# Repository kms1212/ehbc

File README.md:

# !IMPORTANT: This project is migrated to Organization [ExtensibleHomeBrewComputer](https://github.com/ExtensibleHomeBrewComputer).

**ARCHIVED**

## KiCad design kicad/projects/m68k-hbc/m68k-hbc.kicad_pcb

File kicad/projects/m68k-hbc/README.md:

# EHBC Motherboard

## Main Goals
- A rich-function homebrew computer with completely extensible specification
- ATX-dimension compatible motherboard
- Configurable firmware
- Dual-boot function with Linux and custom multitasking OS
- Four 72-pin SIMM DRAM slots
- Rich peripheral interconnection features
  - MMIO with custom address configuration
  - Custom PCI-like expansion port (PEP, Peripheral Expansion Port)
  - 16-bit ISA bus
  - 8/16-bit PP Bus for low-speed peripherals
  - Floppy, IDE, RS232, UART, USB, Ethernet, Audio, etc.
- Advanced Memory Features
  - DRAM Controller with FPM and Read-Modify-Write support
  - 8-channel DMA support
- TBD

## Major ICs
- Main CPU MC68030 (@ 25, 33, 50MHz)
- Floating-point coprocessor MC68882 (@ 25, 33, 50MHz)
- Two EPF6016QC240 implementing some important features, as follows:
  - DRAM & 8-Channel DMA Controller with Cache
  - System Bus Controller (Processor Local Bus, PEP, ISA, OPB, ATA)
- ATMega32-16P working as a System Master Controller
- RTL8019AS ethernet controller
- CS4231A audio codec
- SL811HS USB host controller
- MC68901 MFP (system timer, USART, and GPIO or interrupt)
- VT82C42 keyboard and mouse controller
- PC8477BV floppy disk controller
- DS1307 RTC
- 25LC256 EEPROM
- PAC1932 power monitor
- EMC1701 power monitor with temperature sensor
- ADP5050 programmable DC-DC buck converter
- MX8315 configurable clock generator
- Auxillary ICS551, 542, and 501s for clock generation
- TBD

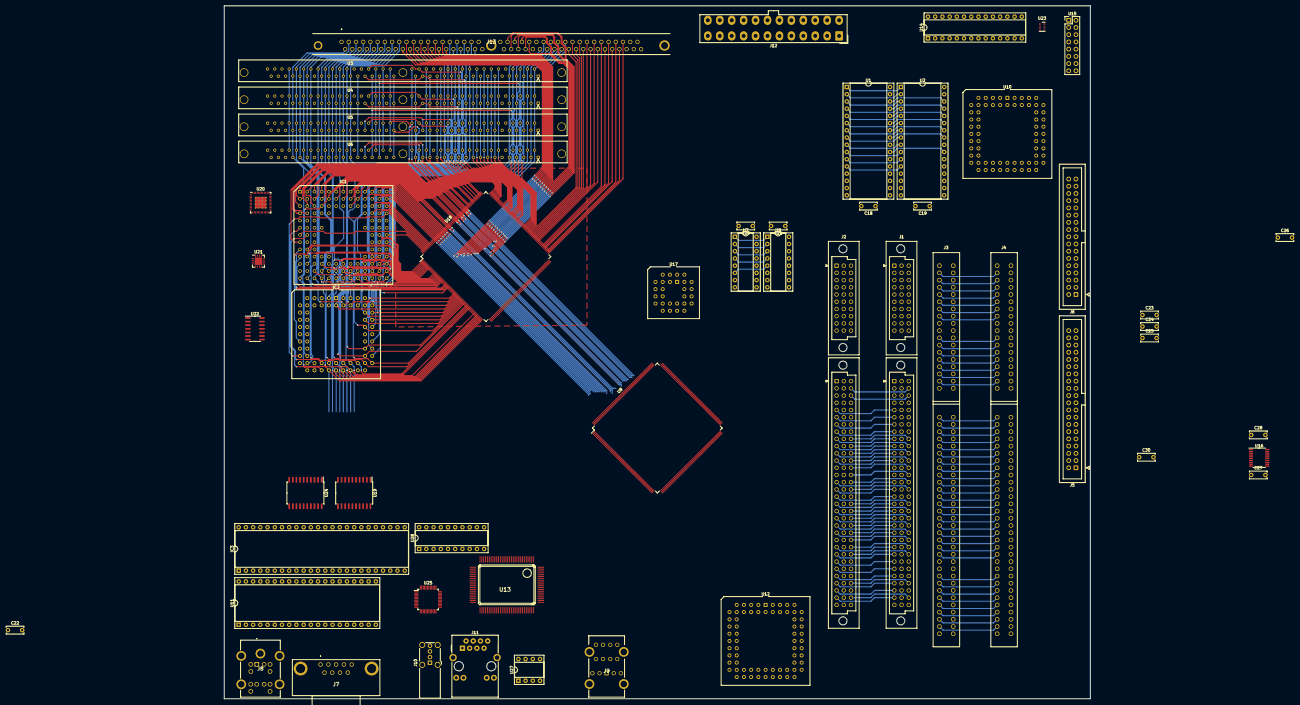
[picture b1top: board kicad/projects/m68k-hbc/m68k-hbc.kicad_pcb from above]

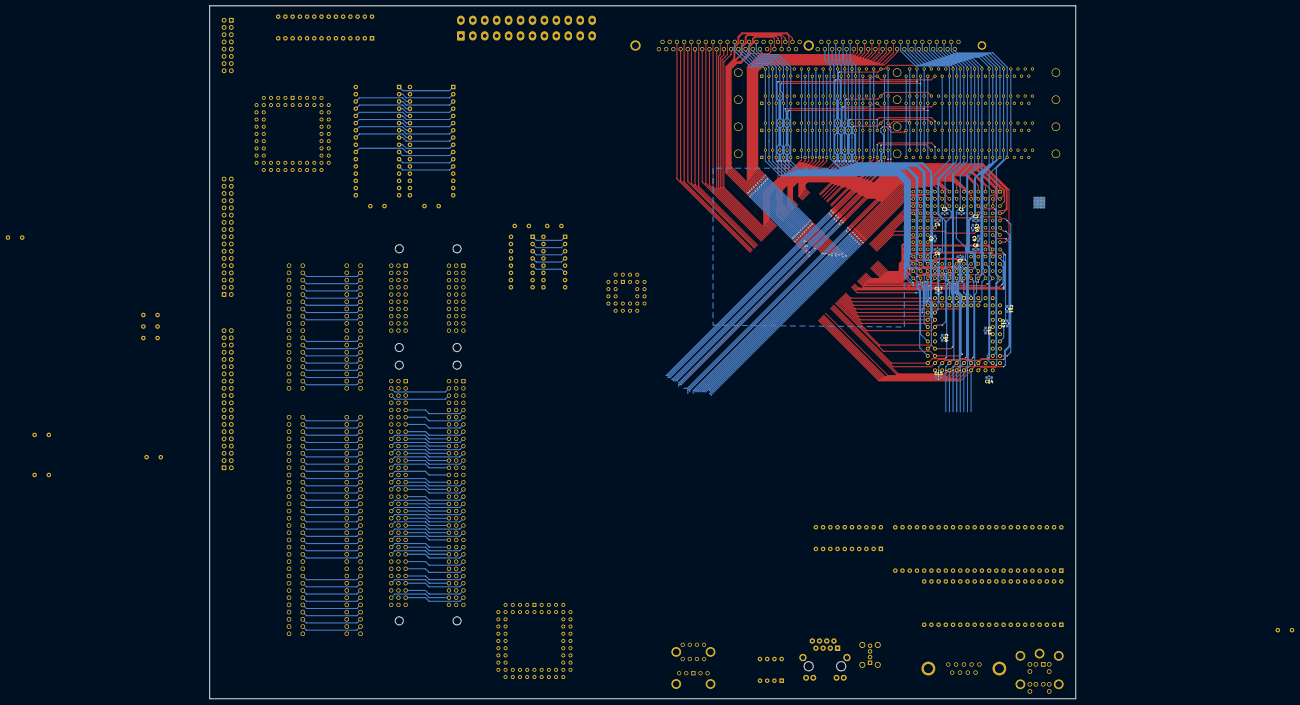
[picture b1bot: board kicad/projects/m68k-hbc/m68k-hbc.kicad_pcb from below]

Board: 6 copper layers, 304.8 x 243.8 mm, 72 parts (17 on the bottom side), 227 nets.

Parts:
C1, C2, C3, C4, C5, C6, C7, C8, C9, C10, C11, C12, C13, C14, C15, C16, C17: 100n; C_0603_1608Metric_Pad1.08x0.95mm_HandSolder
C18, C19, C20, C21, C22, C23, C24, C25, C26, C27, C28, C30: 100n; C_Disc_D6.0mm_W2.5mm_P5.00mm
IC1: MC68030RC; PGA128
IC2: MC68881FN; PLCC-68_THT-Socket
IC3: MC68901P; DIP-48_W15.24mm_Socket
J1, J2: PEP_Data_DIN41612_3x32; PEP_Board
J3, J4: Bus_ISA_16bit; ISA_16bit
J5: IDC_PATA; IDC-Header_2x20_P2.54mm_Vertical
J6: IDC_FDD; IDC-Header_2x17_P2.54mm_Vertical
J7: 5747840-4; 57478404
J8: KMDGX-6SG_P-S4N; KMDGX6SGPS4N
J9: STX-4335-5BGP-S1; STX43355BGPS1
J10: USB_A; USB_A_Wuerth_614004134726_Horizontal
J11: RJ45_Bel_SI-60062-F
J12: ATX-24; Molex_Mini-Fit_Jr_5566-24A_2x12_P4.20mm_Vertical
J13: SIMM80_Cache; 58220304
U1, U2: SST39SF040; DIP-32_W15.24mm_Socket
U3, U4, U5, U6: SIMM72
U7, U9: 74LS138; DIP-16_W7.62mm_Socket
U8, U18: EPF6016QC240; PQFP-240_32.1x32.1mm_P0.5mm
U10: PC8477BV; PLCC-68_THT-Socket
U11: VT82C42; DIP-40_W15.24mm_Socket
U12: CS4231A; PLCC-68_THT-Socket
U13: RTL8019AS
U14: ATmega328P-P; DIP-28_W7.62mm_Socket
U15: SYS_Header; PinHeader_2x08_P2.54mm_Vertical
U16: PCA9564; TSSOP-20_4.4x6.5mm_P0.65mm
U17: TP3465V; PLCC-28_THT-Socket
U19, U24: 74LS245; SOIC-20W_7.5x12.8mm_P1.27mm
U20: ADP5050ACPZ; LFCSP-48-1EP_7x7mm_P0.5mm_EP4.1x4.1mm_ThermalVias
U21: PAC1932x-xJQ; UQFN-16-1EP_4x4mm_P0.65mm_EP2.6x2.6mm
U22: MX8315MC; SOIC-14_3.9x8.7mm_P1.27mm
U23: STM6601; TDFN-12_2x3mm_P0.5mm
U25: SL811HST; TQFP-48_7x7mm_P0.5mm
U27: 93CxxC; DIP-8_W7.62mm_Socket
U28: PAL16L8; DIP-20_W7.62mm_Socket

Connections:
+3.3V: J1.Pa8 (+3.3V), J1.Pa9 (+3.3V), J1.Pb8 (+3.3V), J1.Pb9 (+3.3V), J1.Pc8 (+3.3V), J1.Pc9 (+3.3V), J2.Pa8 (+3.3V), J2.Pa9 (+3.3V), J2.Pb8 (+3.3V), J2.Pb9 (+3.3V), J2.Pc8 (+3.3V), J2.Pc9 (+3.3V), J12.1 (+3.3V), J12.2 (+3.3V), J12.12 (+3.3V), J12.13 (+3.3V)
+5V: IC2.18 (SIZE), IC2.26 (A0), J1.Pa5 (+5V), J1.Pa6 (+5V), J1.Pa7 (+5V), J1.Pb7 (+5V), J1.Pc5 (+5V), J1.Pc6 (+5V), J1.Pc7 (+5V), J2.Pa5 (+5V), J2.Pa6 (+5V), J2.Pa7 (+5V), J2.Pb7 (+5V), J2.Pc5 (+5V), J2.Pc6 (+5V), J2.Pc7 (+5V), J3.3 (+5V), J3.29 (VCC), J3.78 (+5V), J4.3 (+5V), J4.29 (VCC), J4.78 (+5V), J12.4 (+5V), J12.6 (+5V), J12.21 (+5V), J12.22 (+5V), J12.23 (+5V), U1.31 (PGM), U2.31 (PGM), U9.6 (E3), U13.13 (SA7), U13.15 (SA8), U13.65 (JP)
+5VCPU: C1.1, C2.1, C3.1, C4.1, C5.1, C6.1, C7.1, C8.1, C9.1, C10.1, C11.1, C12.1, C13.1, C14.1, C15.1, C16.1, C17.1, C18.1, C19.1, IC1.C06 (VCC@1), IC1.D04 (VCC@2), IC1.D10 (VCC@3), IC1.F02 (VCC@4), IC1.F11 (VCC@5), IC1.H03 (VCC@6), IC1.H11 (VCC@7), IC1.K04 (VCC@8), IC1.K10 (VCC@9), IC1.L06 (VCC@10), IC2.10 (VCC@1), IC2.16 (VCC@2), IC2.17 (VCC@3), IC2.27 (VCC@4), IC2.43 (VCC@5), IC2.52 (VCC@6), IC2.53 (VCC@7), IC2.61 (VCC@8)
+5VMEM: J13.39 (+5V), J13.40 (+5V), J13.41 (+5V), U1.32 (VCC), U2.32 (VCC), U3.10 (+3.3V/+5V), U3.30 (+3.3V/+5V), U3.59 (+3.3V/+5V), U4.10 (+3.3V/+5V), U4.30 (+3.3V/+5V), U4.59 (+3.3V/+5V), U5.10 (+3.3V/+5V), U5.30 (+3.3V/+5V), U5.59 (+3.3V/+5V), U6.10 (+3.3V/+5V), U6.30 (+3.3V/+5V), U6.59 (+3.3V/+5V)
+5VPER: C20.1, C21.1, C22.1, C23.1, C24.1, C25.1, C26.1, C27.1, C28.1, C30.1, IC3.11 (VCC), U7.16 (VCC), U9.16 (VCC), U10.18 (+5V), U10.60 (+5V), U10.68 (+5V), U11.40 (+5V), U13.6 (+5V), U13.17 (+5V), U13.47 (+5V), U13.57 (+5V), U13.70 (+5V), U13.89 (+5V), U14.7 (VCC), U16.20 (VCC), U17.28 (VCC), U19.20 (VCC), U22.9 (DVDD), U24.20 (VCC), U27.6 (ORG), U27.8 (VCC)
+5VSB: J1.Pa4 (+5VSB), J2.Pa4 (+5VSB), J12.9 (+5VSB), U23.1 (Vcc)
+12V: J1.Pa2 (+12V), J1.Pa3 (+12V), J1.Pb2 (+12V), J1.Pb3 (+12V), J1.Pc2 (+12V), J1.Pc3 (+12V), J2.Pa2 (+12V), J2.Pa3 (+12V), J2.Pb2 (+12V), J2.Pb3 (+12V), J2.Pc2 (+12V), J2.Pc3 (+12V), J3.9 (+12V), J4.9 (+12V), J12.10 (+12V), J12.11 (+12V)
-5V: J1.Pc4 (-5V), J2.Pc4 (-5V), J3.5 (-5V), J4.5 (-5V)
-12V: J1.Pb4 (-12V), J2.Pb4 (-12V), J3.7 (-12V), J4.7 (-12V), J12.14 (-12V)
/Bus/A0: IC1.A02 (A0), IC3.2 (RS1), U10.7 (A0), U11.9 (A0), U12.10 (A0), U16.14 (A0), U18.197 (IO), U25.42 (A0)
/Bus/A1: IC1.C04 (A1), IC2.25 (A1), IC3.3 (RS2), U1.12 (A0), U2.12 (A0), U10.8 (A1), U12.9 (A1), U16.15 (A1), U18.203 (IO)
/Bus/A2: IC1.D13 (A2), IC2.24 (A2), IC3.4 (RS3), U1.11 (A1), U2.11 (A1), U10.10 (A2), U18.237 (IO)
/Bus/A3: IC1.D12 (A3), IC2.23 (A3), IC3.5 (RS4), U1.10 (A2), U2.10 (A2), U18.236 (IO)
/Bus/A4: IC1.C13 (A4), IC2.22 (A4), IC3.6 (RS5), U1.9 (A3), U2.9 (A3), U18.234 (IO)
/Bus/A5: IC1.C12 (A5), U1.8 (A4), U2.8 (A4), U18.233 (IO)
/Bus/A6: IC1.D11 (A6), U1.7 (A5), U2.7 (A5), U18.235 (IO)
/Bus/A7: IC1.B13 (A7), U1.6 (A6), U2.6 (A6), U18.228 (IO)
/Bus/A8: IC1.B12 (A8), U1.5 (A7), U2.5 (A7), U7.1 (A0), U9.1 (A0), U18.227 (IO)
/Bus/A9: IC1.C11 (A9), U1.27 (A8), U2.27 (A8), U7.2 (A1), U9.2 (A1), U18.232 (IO)
/Bus/A10: IC1.A13 (A10), U1.26 (A9), U2.26 (A9), U7.3 (A2), U9.3 (A2), U18.224 (IO)
/Bus/A11: IC1.C10 (A11), U1.23 (A10), U2.23 (A10), U7.6 (E3), U9.5 (E2), U18.231 (IO)
/Bus/A12: IC1.B11 (A12), J13.18 (A0), U1.25 (A11), U2.25 (A11), U18.226 (IO)
/Bus/A13: IC1.A12 (A13), J13.19 (A1), U1.4 (A12), U2.4 (A12), U18.223 (IO)
/Bus/A14: IC1.B10 (A14), J13.20 (A2), U1.28 (A13), U2.28 (A13), U18.225 (IO)
/Bus/A15: IC1.A11 (A15), J13.21 (A3), U1.29 (A14), U2.29 (A14), U18.222 (IO)
/Bus/A16: IC1.B09 (A16), J13.22 (A4), U1.3 (A15), U2.3 (A15), U18.220 (IO)
/Bus/A17: IC1.A10 (A17), J13.23 (A5), U1.2 (A16), U2.2 (A16), U18.221 (IO)
/Bus/A18: IC1.C08 (A18), J13.24 (A6), U1.30 (A17), U2.30 (A17), U18.218 (IO)
/Bus/A19: IC1.A09 (A19), J13.25 (A7), U1.1 (A18), U2.1 (A18), U18.219 (IO)
/Bus/A20: IC1.B08 (A20), J13.26 (A8), U18.217 (IO)
/Bus/A21: IC1.A08 (A21), J13.27 (A9), U18.215 (IO)
/Bus/A22: IC1.B07 (A22), J13.28 (A10), U18.214 (IO)
/Bus/A23: IC1.A07 (A23), J13.29 (A11), U18.213 (IO)
/Bus/A24: IC1.A06 (A24), J13.30 (A12), U18.207 (IO)
/Bus/A25: IC1.B06 (A25), J13.43 (A13), U18.208 (IO)
/Bus/A26: IC1.A05 (A26), J13.44 (A14), U18.204 (IO)
/Bus/A27: IC1.B05 (A27), J13.45 (A15), U18.206 (IO)
/Bus/A28: IC1.A04 (A28), J13.46 (A16), U18.201 (IO)
/Bus/A29: IC1.B04 (A29), J13.47 (A17), U18.202 (IO)
/Bus/A30: IC1.A03 (A30), J13.48 (A18), U18.198 (IO)
/Bus/A31: IC1.B03 (A31), J13.49 (A19), U18.199 (IO)
/Bus/D0: IC1.K13 (D0), IC2.3 (D0), J13.52 (D24), U1.13 (D0), U3.9 (DQ19), U4.9 (DQ19), U5.9 (DQ19), U6.9 (DQ19), U18.8 (IO)
/Bus/D1: IC1.K12 (D1), IC2.2 (D1), J13.36 (D21), U1.14 (D1), U3.22 (DQ5), U4.22 (DQ5), U5.22 (DQ5), U6.22 (DQ5), U18.36 (IO)
/Bus/D2: IC1.L13 (D2), IC2.1 (D2), J13.53 (D25), U1.15 (D2), U3.8 (DQ3), U4.8 (DQ3), U5.8 (DQ3), U6.8 (DQ3), U18.15 (IO)
/Bus/D3: IC1.M13 (D3), IC2.68 (D3), J13.55 (D27), U1.17 (D3), U3.6 (DQ2), U4.6 (DQ2), U5.6 (DQ2), U6.6 (DQ2), U18.17 (IO)
/Bus/D4: IC1.L12 (D4), IC2.67 (D4), J13.37 (D22), U1.18 (D4), U3.21 (DQ20), U4.21 (DQ20), U5.21 (DQ20), U6.21 (DQ20), U18.14 (IO)
/Bus/D5: IC1.K11 (D5), IC2.66 (D5), J13.32 (D17), U1.19 (D5), U3.26 (DQ7), U4.26 (DQ7), U5.26 (DQ7), U6.26 (DQ7), U18.33 (IO)
/Bus/D6: IC1.M12 (D6), IC2.65 (D6), J13.38 (D23), U1.20 (D6), U3.20 (DQ4), U4.20 (DQ4), U5.20 (DQ4), U6.20 (DQ4), U18.16 (IO)
/Bus/D7: IC1.L11 (D7), IC2.64 (D7), J13.34 (D19), U1.21 (D7), U3.24 (DQ6), U4.24 (DQ6), U5.24 (DQ6), U6.24 (DQ6), U18.13 (IO)
/Bus/D8: IC1.N13 (D8), IC2.62 (D8), J13.57 (D29), U2.13 (D0), U3.4 (DQ1), U4.4 (DQ1), U5.4 (DQ1), U6.4 (DQ1), U18.34 (IO)
/Bus/D9: IC1.M11 (D9), IC2.60 (D9), J13.35 (D20), U2.14 (D1), U3.23 (DQ21), U4.23 (DQ21), U5.23 (DQ21), U6.23 (DQ21), U18.35 (IO)
/Bus/D10: IC1.L10 (D10), IC2.59 (D10), J13.17 (D15), U2.15 (D2), U3.49 (DQ8), U4.49 (DQ8), U5.49 (DQ8), U6.49 (DQ8), U18.38 (IO)
/Bus/D11: IC1.N12 (D11), IC2.58 (D11), J13.54 (D26), U2.17 (D3), U3.7 (DQ18), U4.7 (DQ18), U5.7 (DQ18), U6.7 (DQ18), U18.37 (IO)
/Bus/D12: IC1.M10 (D12), IC2.57 (D12), J13.31 (D16), U2.18 (D4), U3.27 (DQ23), U4.27 (DQ23), U5.27 (DQ23), U6.27 (DQ23), U18.40 (IO)
/Bus/D13: IC1.N11 (D13), IC2.56 (D13), J13.33 (D18), U2.19 (D5), U3.25 (DQ22), U4.25 (DQ22), U5.25 (DQ22), U6.25 (DQ22), U18.39 (IO)
/Bus/D14: IC1.M09 (D14), IC2.55 (D14), J13.15 (D13), U2.20 (D6), U3.51 (DQ9), U4.51 (DQ9), U5.51 (DQ9), U6.51 (DQ9), U18.41 (IO)
/Bus/D15: IC1.N10 (D15), IC2.54 (D15), J13.58 (D30), U2.21 (D7), U3.3 (DQ16), U4.3 (DQ16), U5.3 (DQ16), U6.3 (DQ16), U18.18 (IO)
/Bus/D16: IC1.N09 (D16), IC2.50 (D16), J13.16 (D14), U3.50 (DQ24), U4.50 (DQ24), U5.50 (DQ24), U6.50 (DQ24), U18.19 (IO), U24.2 (A0)
/Bus/D17: IC1.M08 (D17), IC2.49 (D17), J13.56 (D28), U3.5 (DQ17), U4.5 (DQ17), U5.5 (DQ17), U6.5 (DQ17), U18.42 (IO), U24.3 (A1)
/Bus/D18: IC1.N08 (D18), IC2.48 (D18), J13.59 (D31), U3.2 (DQ0), U4.2 (DQ0), U5.2 (DQ0), U6.2 (DQ0), U18.20 (IO), U24.4 (A2)
/Bus/D19: IC1.N07 (D19), IC2.47 (D19), J13.14 (D12), U3.52 (DQ25), U4.52 (DQ25), U5.52 (DQ25), U6.52 (DQ25), U18.43 (IO), U24.5 (A3)
/Bus/D20: IC1.M07 (D20), IC2.46 (D20), J13.13 (D11), U3.53 (DQ10), U4.53 (DQ10), U5.53 (DQ10), U6.53 (DQ10), U18.27 (IO), U24.6 (A4)
/Bus/D21: IC1.N06 (D21), IC2.45 (D21), J13.12 (D10), U3.54 (DQ26), U4.54 (DQ26), U5.54 (DQ26), U6.54 (DQ26), U18.46 (IO), U24.7 (A5)
/Bus/D22: IC1.M06 (D22), IC2.44 (D22), J13.11 (D9), U3.55 (DQ11), U4.55 (DQ11), U5.55 (DQ11), U6.55 (DQ11), U18.45 (IO), U24.8 (A6)
/Bus/D23: IC1.N05 (D23), IC2.42 (D23), J13.10 (D8), U3.56 (DQ27), U4.56 (DQ27), U5.56 (DQ27), U6.56 (DQ27), U18.47 (IO), U24.9 (A7)
/Bus/D24: IC1.M05 (D24), IC2.40 (D24), J13.9 (D7), U3.57 (DQ12), U4.57 (DQ12), U5.57 (DQ12), U6.57 (DQ12), U18.48 (IO), U19.2 (A0)
/Bus/D25: IC1.N04 (D25), IC2.39 (D25), J13.6 (D4), U3.61 (DQ13), U4.61 (DQ13), U5.61 (DQ13), U6.61 (DQ13), U18.53 (IO), U19.3 (A1)
/Bus/D26: IC1.N03 (D26), IC2.38 (D26), J13.5 (D3), U3.62 (DQ30), U4.62 (DQ30), U5.62 (DQ30), U6.62 (DQ30), U18.55 (IO), U19.4 (A2)
/Bus/D27: IC1.M04 (D27), IC2.37 (D27), J13.8 (D6), U3.58 (DQ28), U4.58 (DQ28), U5.58 (DQ28), U6.58 (DQ28), U18.56 (IO), U19.5 (A3)
/Bus/D28: IC1.N02 (D28), IC2.36 (D28), J13.3 (D1), U3.64 (DQ31), U4.64 (DQ31), U5.64 (DQ31), U6.64 (DQ31), U18.57 (IO), U19.6 (A4)
/Bus/D29: IC1.M03 (D29), IC2.35 (D29), J13.4 (D2), U3.63 (DQ14), U4.63 (DQ14), U5.63 (DQ14), U6.63 (DQ14), U18.58 (IO), U19.7 (A5)
/Bus/D30: IC1.L04 (D30), IC2.34 (D30), J13.7 (D5), U3.60 (DQ29), U4.60 (DQ29), U5.60 (DQ29), U6.60 (DQ29), U18.59 (IO), U19.8 (A6)
/Bus/D31: IC1.N01 (D31), IC2.33 (D31), J13.2 (D0), U3.65 (DQ15), U4.65 (DQ15), U5.65 (DQ15), U6.65 (DQ15), U18.60 (IO), U19.9 (A7)
/Bus/FC0: IC1.D02 (FC0), U18.185 (IO)
/Bus/FC1: IC1.C01 (FC1), U18.187 (IO)
/Bus/FC2: IC1.D01 (FC2), U18.183 (IO)
/Bus/ISA/A20: J3.85 (LA20), J4.85 (LA20)
/Bus/ISA/A21: J3.84 (LA21), J4.84 (LA21)
/Bus/ISA/A22: J3.83 (LA22), J4.83 (LA22)
/Bus/ISA/A23: J3.82 (LA23), J4.82 (LA23)
/Bus/ISA/OSC: J3.30 (OSC), J4.30 (OSC)
/Bus/ISA/RST: J3.2 (RESET), J4.2 (RESET)
/Bus/MMIO/BD0: IC3.37 (D0), U10.11 (D0), U11.12 (D0), U12.6 (D0), U16.1 (D0), U24.18 (B0), U25.21 (D0)
/Bus/MMIO/BD1: IC3.38 (D1), U10.13 (D1), U11.13 (D1), U12.5 (D1), U16.2 (D1), U24.17 (B1), U25.27 (D1)
/Bus/MMIO/BD2: IC3.39 (D2), U10.14 (D2), U11.14 (D2), U12.4 (D2), U16.3 (D2), U24.16 (B2), U25.28 (D2)
/Bus/MMIO/BD3: IC3.40 (D3), U10.15 (D3), U11.15 (D3), U12.3 (D3), U16.4 (D3), U24.15 (B3), U25.29 (D3)
/Bus/MMIO/BD4: IC3.41 (D4), U10.17 (D4), U11.16 (D4), U12.68 (D4), U16.5 (D4), U24.14 (B4), U25.31 (D4)
/Bus/MMIO/BD5: IC3.42 (D5), U10.19 (D5), U11.17 (D5), U12.67 (D5), U16.6 (D5), U24.13 (B5), U25.32 (D5)
/Bus/MMIO/BD6: IC3.43 (D6), U10.20 (D6), U11.18 (D6), U12.66 (D6), U16.7 (D6), U24.12 (B6), U25.33 (D6)
/Bus/MMIO/BD7: IC3.44 (D7), U10.22 (D7), U11.19 (D7), U12.65 (D7), U16.8 (D7), U24.11 (B7), U25.39 (D7)
/Bus/MMIO/Ethernet/IOCHRDY: U13.35 (IOCHRDY), U28.11 (I10)
/Bus/MMIO/Ethernet/~CS: U13.34 (~AEN), U28.2 (I2)
/Bus/MMIO/Ethernet/~IOR: U13.29 (~IOR), U28.15 (IO5)
/Bus/MMIO/Ethernet/~IOW: U13.30 (~IOW), U28.14 (IO6)
/Bus/MMIO/Ethernet/~RST: U13.33 (RST), U28.16 (IO4)
/Bus/MMIO/Ethernet/~SMEMR: U13.31 (~SMEMR), U28.13 (IO7)
/Bus/MMIO/Ethernet/~SMEMW: U13.32 (~SMEMW), U28.12 (IO8)
/Bus/MMIO/~EN: U7.4 (E1), U9.4 (E1)
/Bus/MMIO/~RD: U10.4 (~RD), U11.8 (~RD), U12.60 (~RD), U16.12 (~RD), U25.45 (~RD)
/Bus/MMIO/~WR: U10.5 (~WR), U11.10 (~WR), U12.61 (~WR), U16.11 (~WR), U25.3 (~WR)
/Bus/PEP/AD0: J1.Da31 (AD0), J2.Da31 (AD0), J3.40 (DB0), J4.40 (DB0), J5.17 (DD0)
/Bus/PEP/AD1: J1.Da30 (AD1), J2.Da30 (AD1), J3.39 (DB1), J4.39 (DB1), J5.15 (DD1)
/Bus/PEP/AD2: J1.Da29 (AD2), J2.Da29 (AD2), J3.38 (DB2), J4.38 (DB2), J5.13 (DD2)
/Bus/PEP/AD3: J1.Da28 (AD3), J2.Da28 (AD3), J3.37 (DB3), J4.37 (DB3), J5.11 (DD3)
/Bus/PEP/AD4: J1.Da27 (AD4), J2.Da27 (AD4), J3.36 (DB4), J4.36 (DB4), J5.9 (DD4)
/Bus/PEP/AD5: J1.Da26 (AD5), J2.Da26 (AD5), J3.35 (DB5), J4.35 (DB5), J5.7 (DD5)
/Bus/PEP/AD6: J1.Da25 (AD6), J2.Da25 (AD6), J3.34 (DB6), J4.34 (DB6), J5.5 (DD6)
/Bus/PEP/AD7: J1.Da24 (AD7), J2.Da24 (AD7), J3.33 (DB7), J4.33 (DB7), J5.3 (DD7)
/Bus/PEP/AD8: J1.Da22 (AD8), J2.Da22 (AD8), J3.91 (D8), J4.91 (D8), J5.4 (DD8)
/Bus/PEP/AD9: J1.Da21 (AD9), J2.Da21 (AD9), J3.92 (D9), J4.92 (D9), J5.6 (DD9)
/Bus/PEP/AD10: J1.Da20 (AD10), J2.Da20 (AD10), J3.93 (D10), J4.93 (D10), J5.8 (DD10)
/Bus/PEP/AD11: J1.Da19 (AD11), J2.Da19 (AD11), J3.94 (D11), J4.94 (D11), J5.10 (DD11)
/Bus/PEP/AD12: J1.Da18 (AD12), J2.Da18 (AD12), J3.95 (D12), J4.95 (D12), J5.12 (DD12)
/Bus/PEP/AD13: J1.Da17 (AD13), J2.Da17 (AD13), J3.96 (D13), J4.96 (D13), J5.14 (DD13)
/Bus/PEP/AD14: J1.Da16 (AD14), J2.Da16 (AD14), J3.97 (D14), J4.97 (D14), J5.16 (DD14)
/Bus/PEP/AD15: J1.Da15 (AD15), J2.Da15 (AD15), J3.98 (D15), J4.98 (D15), J5.18 (DD15)
/Bus/PEP/AD16: J1.Dc25 (AD16), J2.Dc25 (AD16), J3.62 (BA00), J4.62 (BA00), J5.35 (DA0)
/Bus/PEP/AD17: J1.Dc24 (AD17), J2.Dc24 (AD17), J3.61 (BA01), J4.61 (BA01), J5.33 (DA1)
/Bus/PEP/AD18: J1.Dc23 (AD18), J2.Dc23 (AD18), J3.60 (BA02), J4.60 (BA02), J5.36 (DA2)
/Bus/PEP/AD19: J1.Dc22 (AD19), J2.Dc22 (AD19), J3.59 (BA03), J4.59 (BA03)
/Bus/PEP/AD20: J1.Dc21 (AD20), J2.Dc21 (AD20), J3.58 (BA04), J4.58 (BA04)
/Bus/PEP/AD21: J1.Dc20 (AD21), J2.Dc20 (AD21), J3.57 (BA05), J4.57 (BA05)
/Bus/PEP/AD22: J1.Dc19 (AD22), J2.Dc19 (AD22), J3.56 (BA06), J4.56 (BA06)
/Bus/PEP/AD23: J1.Dc18 (AD23), J2.Dc18 (AD23), J3.55 (BA07), J4.55 (BA07)
/Bus/PEP/AD24: J1.Dc16 (AD24), J2.Dc16 (AD24), J3.54 (BA08), J4.54 (BA08)
/Bus/PEP/AD25: J1.Dc15 (AD25), J2.Dc15 (AD25), J3.53 (BA09), J4.53 (BA09)
/Bus/PEP/AD26: J1.Dc14 (AD26), J2.Dc14 (AD26), J3.52 (BA10), J4.52 (BA10)
/Bus/PEP/AD27: J1.Dc13 (AD27), J2.Dc13 (AD27), J3.51 (BA11), J4.51 (BA11)
/Bus/PEP/AD28: J1.Dc12 (AD28), J2.Dc12 (AD28), J3.50 (BA12), J4.50 (BA12)
/Bus/PEP/AD29: J1.Dc11 (AD29), J2.Dc11 (AD29), J3.49 (BA13), J4.49 (BA13)
/Bus/PEP/AD30: J1.Dc10 (AD30), J2.Dc10 (AD30), J3.48 (BA14), J4.48 (BA14)
/Bus/PEP/AD31: J1.Dc9 (AD31), J2.Dc9 (AD31), J3.47 (BA15), J4.47 (BA15)
/Bus/PEP/CLK: J1.Dc2 (CLK), J2.Dc2 (CLK)
/Bus/PEP/OP0: J1.Da10 (OP0), J2.Da10 (OP0), J3.46 (BA16), J4.46 (BA16)
/Bus/PEP/OP1: J1.Da9 (OP1), J2.Da9 (OP1), J3.45 (BA17), J3.88 (LA17), J4.45 (BA17), J4.88 (LA17)
/Bus/PEP/OP2: J1.Da8 (OP2), J2.Da8 (OP2), J3.44 (BA18), J3.87 (LA18), J4.44 (BA18), J4.87 (LA18)
/Bus/PEP/OP3: J1.Da7 (OP3), J2.Da7 (OP3), J3.43 (BA19), J3.86 (LA19), J4.43 (BA19), J4.86 (LA19)
/Bus/PEP/PAR: J1.Dc31 (PAR), J2.Dc31 (PAR)
/Bus/PEP/~CRDY: J1.Da12 (~CRDY), J2.Da12 (~CRDY)
/Bus/PEP/~INIT: J1.Da6 (~INIT), J2.Da6 (~INIT)
/Bus/PEP/~MRDY: J1.Da11 (~MRDY), J2.Da11 (~MRDY)
/Bus/PEP/~PERR: J1.Dc29 (~PERR), J2.Dc29 (~PERR)
/Bus/PEP/~PRES0: J1.Da2 (~PRES), J1.Pb6 (~PRES)
/Bus/PEP/~PRES1: J2.Da2 (~PRES), J2.Pb6 (~PRES)
/Bus/PEP/~RST: J1.Dc3 (~RST), J2.Dc3 (~RST)
/Bus/PEP/~STOP: J1.Da5 (~STOP), J2.Da5 (~STOP)
/Bus/SIZ0: IC1.L02 (SIZ0), U18.6 (IO)
/Bus/SIZ1: IC1.K03 (SIZ1), U18.7 (IO)
/Bus/~IPL0: IC1.H13 (IPL0), U18.3 (IO)
/Bus/~IPL1: IC1.G13 (IPL1), U18.239 (IO)
/Bus/~IPL2: IC1.G12 (IPL2), U18.1 (IO)
/Memory/SIMM/~EDO: U3.66 (~EDO/NC), U4.66 (~EDO/NC), U5.66 (~EDO/NC), U6.66 (~EDO/NC)
/Memory/SIMM/~WE: U3.47 (~WE), U4.47 (~WE), U5.47 (~WE), U6.47 (~WE)
/Memory/SIMM_PDQ0: U3.36 (PDQ0/NC), U4.36 (PDQ0/NC), U5.36 (PDQ0/NC), U6.36 (PDQ0/NC), U18.179 (IO)
/Memory/SIMM_PDQ1: U3.37 (PDQ1/NC), U4.37 (PDQ1/NC), U5.37 (PDQ1/NC), U6.37 (PDQ1/NC), U18.177 (IO)
/Memory/SIMM_PDQ2: U3.35 (PDQ2/NC), U4.35 (PDQ2/NC), U5.35 (PDQ2/NC), U6.35 (PDQ2/NC), U18.178 (IO)
/Memory/SIMM_PDQ3: U3.38 (PDQ3/NC), U4.38 (PDQ3/NC), U5.38 (PDQ3/NC), U6.38 (PDQ3/NC), U18.180 (IO)
/Memory/SIMM_SA0: U3.12 (A0), U4.12 (A0), U5.12 (A0), U6.12 (A0), U18.145 (IO)
/Memory/SIMM_SA1: U3.13 (A1), U4.13 (A1), U5.13 (A1), U6.13 (A1), U18.146 (IO)
/Memory/SIMM_SA2: U3.14 (A2), U4.14 (A2), U5.14 (A2), U6.14 (A2), U18.147 (IO)
/Memory/SIMM_SA3: U3.15 (A3), U4.15 (A3), U5.15 (A3), U6.15 (A3), U18.153 (IO)
/Memory/SIMM_SA4: U3.16 (A4), U4.16 (A4), U5.16 (A4), U6.16 (A4), U18.154 (IO)
/Memory/SIMM_SA5: U3.17 (A5), U4.17 (A5), U5.17 (A5), U6.17 (A5), U18.156 (IO)
/Memory/SIMM_SA6: U3.18 (A6), U4.18 (A6), U5.18 (A6), U6.18 (A6), U18.157 (IO)
/Memory/SIMM_SA7: U3.28 (A7), U4.28 (A7), U5.28 (A7), U6.28 (A7), U18.167 (IO)
/Memory/SIMM_SA8: U3.31 (A8), U4.31 (A8), U5.31 (A8), U6.31 (A8), U18.173 (IO)
/Memory/SIMM_SA9: U3.32 (A9/NC), U4.32 (A9/NC), U5.32 (A9/NC), U6.32 (A9/NC), U18.174 (IO)
/Memory/SIMM_SA10: U3.19 (A10/NC), U4.19 (A10/NC), U5.19 (A10/NC), U6.19 (A10/NC), U18.158 (IO)
/Memory/SIMM_SA11: U3.29 (A11/NC), U4.29 (A11/NC), U5.29 (A11/NC), U6.29 (A11/NC), U18.168 (IO)
/Memory/SIMM_~CAS0: U3.40 (~CAS0), U4.40 (~CAS0), U5.40 (~CAS0), U6.40 (~CAS0), U18.141 (IO)
/Memory/SIMM_~CAS1: U3.43 (~CAS1), U4.43 (~CAS1), U5.43 (~CAS1), U6.43 (~CAS1), U18.144 (IO)
/Memory/SIMM_~CAS2: U3.41 (~CAS2), U4.41 (~CAS2), U5.41 (~CAS2), U6.41 (~CAS2), U18.142 (IO)
/Memory/SIMM_~CAS3: U3.42 (~CAS3), U4.42 (~CAS3), U5.42 (~CAS3), U6.42 (~CAS3), U18.143 (IO)
/Memory/SIMM_~RAS0: U3.34 (A13/~RAS2/NC), U3.44 (~RAS0), U18.160 (IO)
/Memory/SIMM_~RAS1: U3.33 (A12/~RAS3/NC), U3.45 (~RAS1/NC), U18.159 (IO)
/Memory/SIMM_~RAS2: U4.34 (A13/~RAS2/NC), U4.44 (~RAS0), U18.163 (IO)
/Memory/SIMM_~RAS3: U4.33 (A12/~RAS3/NC), U4.45 (~RAS1/NC), U18.162 (IO)
/Memory/SIMM_~RAS4: U5.34 (A13/~RAS2/NC), U5.44 (~RAS0), U18.165 (IO)
/Memory/SIMM_~RAS5: U5.33 (A12/~RAS3/NC), U5.45 (~RAS1/NC), U18.164 (IO)
/Memory/SIMM_~RAS6: U6.34 (A13/~RAS2/NC), U6.44 (~RAS0), U18.176 (IO)
/Memory/SIMM_~RAS7: U6.33 (A12/~RAS3/NC), U6.45 (~RAS1/NC), U18.175 (IO)
/Memory/TD0: J13.60 (D32), U18.140 (IO)
/Memory/TD1: J13.61 (D33), U18.139 (IO)
/Memory/TD2: J13.62 (D34), U18.138 (IO)
/Memory/TD3: J13.63 (D35), U18.137 (IO)
/Memory/TD4: J13.64 (D36), U18.136 (IO)
/Memory/TD5: J13.65 (D37), U18.135 (IO)
/Memory/TD6: J13.66 (D38), U18.134 (IO)
/Memory/TD7: J13.67 (D39), U18.133 (IO)
/Memory/TD8: J13.68 (D40), U18.132 (IO)
/Memory/TD9: J13.69 (D41), U18.128 (IO)
/Memory/TD10: J13.70 (D42), U18.127 (IO)
/Memory/TD11: J13.71 (D43), U18.126 (IO)
/Memory/TD12: J13.72 (D44), U18.125 (IO)
/Memory/TD13: J13.73 (D45), U18.123 (IO)
/Memory/TD14: J13.74 (D46), U18.122 (IO)
/Memory/TD15: J13.75 (D47), U18.121 (IO)
/Memory/~BERR: IC1.H01 (BERR), U18.182 (IO)
/Memory/~BGACK: IC1.C03 (BGACK), U18.196 (IO)
/Memory/~BG: IC1.B02 (BG), U18.194 (IO)
/Memory/~BR: IC1.A01 (BR), U18.190 (IO)
/Memory/~CBACK: IC1.J01 (CBACK), U18.26 (IO)
/Memory/~CBREQ: IC1.K01 (CBREQ), U18.25 (IO)
/Memory/~CDIS: IC1.H12 (CDIS), U18.2 (IO)
/Memory/~CIIN: IC1.C02 (CIOUT), U18.193 (IO)
/Memory/~CIOUT: IC1.L01 (CIIN), U18.24 (IO)
/Memory/~RMC: IC1.B01 (RMC), U18.189 (IO)
/Memory/~STERM: IC1.G01 (STERM), U18.238 (IO)
/Power/PWR+: U15.14 (PSW+), U23.6 (~PB)
/Power/RST+: U15.10 (RSW+), U23.2 (~SR)
/Processor/CLK: IC1.E01 (CLK), IC2.11 (CLK)
/Processor/R/~W: IC1.L03 (R/W\), IC2.28 (R/W\), U18.21 (IO)
/Processor/~AS: IC1.J02 (AS), IC2.21 (AS), U18.4 (IO)
/Processor/~DSACK0: IC1.F01 (DSACK0), IC2.31 (DSACK0)
/Processor/~DSACK1: IC1.G02 (DSACK1), IC2.32 (DSACK1)
/Processor/~DS: IC1.K02 (DS), IC2.20 (DS), U18.5 (IO)
/Processor/~RST: IC1.F12 (RESET), IC2.13 (RESET)
GND: C1.2, C2.2, C3.2, C4.2, C5.2, C6.2, C7.2, C8.2, C9.2, C10.2, C11.2, C12.2, C13.2, C14.2, C15.2, C16.2, C17.2, C18.2, C19.2, C20.2, C21.2, C22.2, C23.2, C24.2, C25.2, C26.2, C27.2, C28.2, C30.2, IC1.C05 (GND@1), IC1.C07 (GND@2), IC1.C09 (GND@3), IC1.E03 (GND@4), IC1.E11 (GND@5), IC1.F03 (GND@6), IC1.G03 (GND@7), IC1.G11 (GND@8), IC1.J03 (GND@9), IC1.J11 (GND@10), IC1.L05 (GND@11), IC1.L07 (GND@12), IC1.L08 (GND@13), IC1.L09 (GND@14), IC2.5 (GND@1), IC2.6 (GND@2), IC2.7 (GND@3), IC2.8 (GND@4), IC2.9 (GND@5), IC2.12 (GND@6), IC2.14 (GND@7), IC2.19 (GND@8), IC2.30 (GND@9), IC2.41 (GND@10), IC2.51 (GND@11), IC2.63 (GND@12), IC3.36 (GND), J1.Da1 (GND), J1.Da3 (GND), J1.Da14 (GND), J1.Da23 (GND), J1.Da32 (GND), J1.Db1 (GND), J1.Db2 (GND), J1.Db3 (GND), J1.Db4 (GND), J1.Db5 (GND), J1.Db6 (GND), J1.Db7 (GND), J1.Db8 (GND), J1.Db9 (GND), J1.Db10 (GND), J1.Db11 (GND), J1.Db12 (GND), J1.Db13 (GND), J1.Db14 (GND), J1.Db15 (GND), J1.Db16 (GND), J1.Db17 (GND), J1.Db18 (GND), J1.Db19 (GND), J1.Db20 (GND), J1.Db21 (GND), J1.Db22 (GND), J1.Db23 (GND), J1.Db24 (GND), J1.Db25 (GND), J1.Db26 (GND), J1.Db27 (GND), J1.Db28 (GND), J1.Db29 (GND), J1.Db30 (GND), J1.Db31 (GND), J1.Db32 (GND), J1.Dc1 (GND), J1.Dc6 (GND), J1.Dc7 (GND), J1.Dc8 (GND), J1.Dc17 (GND), J1.Dc26 (GND), J1.Dc27 (GND), J1.Dc30 (GND), J1.Dc32 (GND), J1.Pa1 (GND), J1.Pa10 (GND), J1.Pb1 (GND), J1.Pb5 (GND), J1.Pb10 (GND), J1.Pc1 (GND), J1.Pc10 (GND), J2.Da1 (GND), J2.Da3 (GND), J2.Da14 (GND), J2.Da23 (GND), J2.Da32 (GND), J2.Db1 (GND), J2.Db2 (GND), J2.Db3 (GND), J2.Db4 (GND), J2.Db5 (GND), J2.Db6 (GND), J2.Db7 (GND), J2.Db8 (GND), J2.Db9 (GND), J2.Db10 (GND), J2.Db11 (GND), J2.Db12 (GND), J2.Db13 (GND), J2.Db14 (GND), J2.Db15 (GND), J2.Db16 (GND), J2.Db17 (GND), J2.Db18 (GND), J2.Db19 (GND), J2.Db20 (GND), J2.Db21 (GND), J2.Db22 (GND), J2.Db23 (GND), J2.Db24 (GND), J2.Db25 (GND), J2.Db26 (GND), J2.Db27 (GND), J2.Db28 (GND), J2.Db29 (GND), J2.Db30 (GND), J2.Db31 (GND), J2.Db32 (GND), J2.Dc1 (GND), J2.Dc6 (GND), J2.Dc7 (GND), J2.Dc8 (GND), J2.Dc17 (GND), J2.Dc26 (GND), J2.Dc27 (GND), J2.Dc30 (GND), J2.Dc32 (GND), J2.Pa1 (GND), J2.Pa10 (GND), J2.Pb1 (GND), J2.Pb5 (GND), J2.Pb10 (GND), J2.Pc1 (GND), J2.Pc10 (GND), J3.1 (GND), J3.10 (GND), J3.31 (GND), J3.80 (GND), J4.1 (GND), J4.10 (GND), J4.31 (GND), J4.80 (GND), J5.2 (GND), J5.19 (GND), J5.22 (GND), J5.24 (GND), J5.26 (GND), J5.30 (GND), J5.40 (GND), J6.1 (GND)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
unnamed: J11.4 (RD+), U13.59 (TPIN+)
unnamed: J11.6 (RD-), U13.58 (TPIN-)
unnamed: J11.1 (TD+), U13.45 (TPOUT+)
unnamed: J11.3 (TD-), U13.46 (TPOUT-)
unnamed: U13.76 (EECS), U27.1 (CS)
unnamed: U13.78 (EEDI/IRQS0/BD6), U27.3 (DI)
unnamed: U13.77 (EEDO/PL1/BD7), U27.4 (DO)
unnamed: U13.79 (EESK/IRQS1/BD5), U27.2 (SCLK)
unnamed: U21.3 (GND), U21.7 (GND), U21.8 (GND), U21.9 (GND), U21.10 (GND)

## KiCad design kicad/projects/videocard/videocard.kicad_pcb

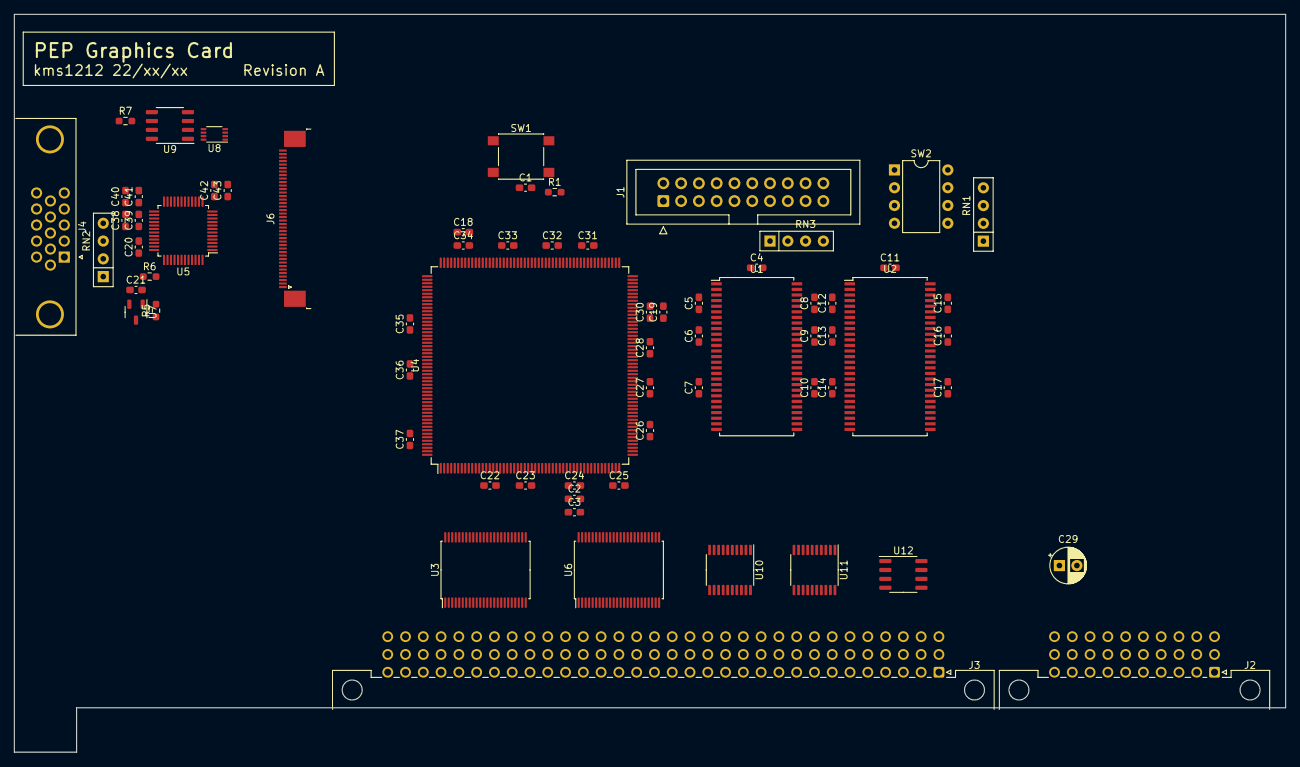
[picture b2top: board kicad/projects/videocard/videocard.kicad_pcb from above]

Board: 4 copper layers, 181.6 x 105.4 mm, 69 parts (0 on the bottom side), 197 nets, no tracks yet.

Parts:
C1, C3, C4, C5, C6, C7, C8, C9, C10, C11, C12, C13, C14, C15, C16, C17, C20, C22, C23, C24, C25, C26, C27, C28, C30, C31, C32, C33, C34, C35, C36, C37, C38, C40, C42: 100n; C_0603_1608Metric_Pad1.08x0.95mm_HandSolder
C2, C21: 1u; C_0603_1608Metric_Pad1.08x0.95mm_HandSolder
C18, C19: 200n; C_0603_1608Metric_Pad1.08x0.95mm_HandSolder
C29: 4.7u; CP_Radial_D5.0mm_P2.50mm
C39, C41, C43: 10n; C_0603_1608Metric_Pad1.08x0.95mm_HandSolder
J1: Conn_ARM_JTAG_SWD_20; IDC-Header_2x10_P2.54mm_Vertical
J2: PEP_Power_DIN41612_3x10; DIN41612_C3_3x10_Male_Horizontal_THT
J3: PEP_Data_DIN41612_3x32; DIN41612_C_3x32_Male_Horizontal_THT
J4: DE15_Receptacle_HighDensity_MountingHoles; DSUB-15-HD_Female_Horizontal_P2.29x1.98mm_EdgePinOffset3.03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
J6: Conn_01x40_MountingPin; TE_4-1734839-0_1x40-1MP_P0.5mm_Horizontal
R1: 10k; R_0603_1608Metric_Pad0.98x0.95mm_HandSolder
R5: 1k; R_0603_1608Metric_Pad0.98x0.95mm_HandSolder
R6: 560; R_0603_1608Metric_Pad0.98x0.95mm_HandSolder
R7: 200k; R_0603_1608Metric_Pad0.98x0.95mm_HandSolder
RN1, RN3: 10k; R_Array_SIP4
RN2: 75; R_Array_SIP4
SW1: SW_SPST; SW_Push_1P1T_NO_6x6mm_H9.5mm
SW2: SW_DIP_x04; DIP-8_W7.62mm
U1, U2: MT48LC16M16A2P; TSOP-II-54_22.2x10.16mm_P0.8mm
U3, U6: 74ALVC164245DGG,51; TSSOP-48_8x12.5mm_P0.5mm
U4: STM32H743BITx; LQFP-208_28x28mm_P0.5mm
U5: ADV7123; LQFP-48_7x7mm_P0.5mm
U7: AD1580BRTZ-REEL7; SOT-23-3
U8: 74LVC2T45DC; VSSOP-8_2.3x2mm_P0.5mm
U9, U12: PCA9306D; SO-8_3.9x4.9mm_P1.27mm
U10, U11: TXS0108EPW; TSSOP-20_4.4x6.5mm_P0.65mm

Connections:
+3.3V: C2.1, C3.1, C4.1, C5.1, C6.1, C7.1, C8.1, C9.1, C10.1, C11.1, C12.1, C13.1, C14.1, C15.1, C16.1, C17.1, C20.2, C22.1, C23.1, C24.1, C25.1, C26.1, C27.1, C28.1, C29.1, C30.1, C31.1, C32.1, C33.1, C34.1, C35.1, C36.1, C37.1, C38.1, C39.1, C40.1, C41.1, C42.1, C43.1, J1.1 (VTREF), J1.2 (VCC/NC), J2.a8 (+3.3V), J2.a9 (+3.3V), J2.b8 (+3.3V), J2.b9 (+3.3V), J2.c8 (+3.3V), J2.c9 (+3.3V), R1.1, R5.1, SW2.1, SW2.2, SW2.3, SW2.4, U1.1 (VDD), U1.3 (VDDQ), U1.9 (VDDQ), U1.14 (VDD), U1.27 (VDD), U1.43 (VDDQ), U1.49 (VDDQ), U2.1 (VDD), U2.3 (VDDQ), U2.9 (VDDQ), U2.14 (VDD), U2.27 (VDD), U2.43 (VDDQ), U2.49 (VDDQ), U4.6 (VBAT), U4.15 (VDD), U4.26 (VDD), U4.39 (VDD), U4.42 (VDDA), U4.52 (VDD), U4.59 (VDD), U4.73 (VDD), U4.83 (VDD), U4.94 (VDD), U4.103 (VDD), U4.115 (VDD), U4.124 (VDD), U4.137 (VDD33_USB), U4.150 (VDD), U4.158 (VDD), U4.171 (VDD), U4.185 (VDD), U4.204 (VDD), U5.13 (VAA), U5.29 (VAA), U5.30 (VAA), U8.1 (VCCA), U8.5 (DIR), U9.2 (VREF1)
+5V: J2.a5 (+5V), J2.a6 (+5V), J2.a7 (+5V), J2.b7 (+5V), J2.c5 (+5V), J2.c6 (+5V), J2.c7 (+5V), R7.1, U8.8 (VCCB), U9.7 (VREF2)
+12V: J2.a2 (+12V), J2.a3 (+12V), J2.b2 (+12V), J2.b3 (+12V), J2.c2 (+12V), J2.c3 (+12V)
/AD0: U3.47 (1A0), U4.154 (PI0)
/AD1: U3.46 (1A1), U4.155 (PI1)
/AD2: U3.44 (1A2), U4.156 (PI2)
/AD3: U3.43 (1A3), U4.157 (PI3)
/AD4: U3.41 (1A4), U4.205 (PI4)
/AD5: U3.40 (1A5), U4.206 (PI5)
/AD6: U3.38 (1A6), U4.207 (PI6)
/AD7: U3.37 (1A7), U4.208 (PI7)
/AD8: U3.36 (2A0), U4.98 (PH8)
/AD9: U3.35 (2A1), U4.99 (PH9)
/AD10: U3.33 (2A2), U4.100 (PH10)
/AD11: U3.32 (2A3), U4.101 (PH11)
/AD12: U3.30 (2A4), U4.102 (PH12)
/AD13: U3.29 (2A5), U4.151 (PH13)
/AD14: U3.27 (2A6), U4.152 (PH14)
/AD15: U3.26 (2A7), U4.153 (PH15)
/AD16: U4.126 (PK0), U6.47 (1A0)
/AD17: U4.127 (PK1), U6.46 (1A1)
/AD18: U4.67 (PJ2), U6.44 (1A2)
/AD19: U4.186 (PK3), U6.43 (1A3)
/AD20: U4.187 (PK4), U6.41 (1A4)
/AD21: U4.95 (PJ5), U6.40 (1A5)
/AD22: U4.118 (PJ6), U6.38 (1A6)
/AD23: U4.190 (PK7), U6.37 (1A7)
/AD24: U4.120 (PJ8), U6.36 (2A0)
/AD25: U4.178 (PG9), U6.35 (2A1)
/AD26: U4.179 (PG10), U6.33 (2A2)
/AD27: U4.180 (PG11), U6.32 (2A3)
/AD28: U4.181 (PG12), U6.30 (2A4)
/AD29: U4.182 (PG13), U6.29 (2A5)
/AD30: U4.183 (PG14), U6.27 (2A6)
/AD31: U4.177 (PJ15), U6.26 (2A7)
/BA0: U1.20 (BA0), U2.20 (BA0), U4.131 (PG4)
/BA1: U1.21 (BA1), U2.21 (BA1), U4.132 (PG5)
/BLUE: J4.3, RN2.4 (R3)
/BOOT0: RN1.2 (R1), SW2.5, U4.197 (BOOT0)
/DDC_SCL: J4.15, U9.6 (SCL2)
/DDC_SDA: J4.12, U9.5 (SDA2)
/DISP_B0: J6.22, U4.3 (PE4), U5.16 (B2)
/DISP_B1: J6.23, U4.144 (PA10), U5.17 (B3)
/DISP_B2: J6.24, U4.141 (PC9), U5.18 (B4)
/DISP_B3: J6.25, U4.142 (PA8), U5.19 (B5)
/DISP_B4: J6.26, U4.175 (PJ13), U5.20 (B6)
/DISP_B5: J6.27, U4.50 (PA3), U5.21 (B7)
/DISP_B6: J6.28, U4.188 (PK5), U5.22 (B8)
/DISP_B7: J6.29, U4.189 (PK6), U5.23 (B9)
/DISP_DE: J6.33, U4.31 (PF10), U5.11 (~BLANK)
/DISP_G0: J6.12, U4.4 (PE5), U5.3 (G2)
/DISP_G1: J6.13, U4.5 (PE6), U5.4 (G3)
/DISP_G2: J6.14, U4.55 (PA6), U5.5 (G4)
/DISP_G3: J6.15, U4.122 (PJ10), U5.6 (G5)
/DISP_G4: J6.16, U4.90 (PB10), U5.7 (G6)
/DISP_G5: J6.17, U4.48 (PH4), U5.8 (G7)
/DISP_G6: J6.18, U4.13 (PI11), U5.9 (G8)
/DISP_G7: J6.19, U4.128 (PK2), U5.10 (G9)
/DISP_HSYNC: J6.36, U4.12 (PI10), U8.3 (2A)
/DISP_PCLK: J6.32, U4.21 (PI14), U5.24 (CLOCK)
/DISP_R0: J6.2, U4.46 (PH2), U5.41 (R2)
/DISP_R1: J6.3, U4.45 (PA2), U5.42 (R3)
/DISP_R2: J6.4, U4.44 (PA1), U5.43 (R4)
/DISP_R3: J6.5, U4.61 (PB0), U5.44 (R5)
/DISP_R4: J6.6, U4.54 (PA5), U5.45 (R6)
/DISP_R5: J6.7, U4.69 (PJ4), U5.46 (R7)
/DISP_R6: J6.8, U4.62 (PB1), U5.47 (R8)
/DISP_R7: J6.9, U4.65 (PJ0), U5.48 (R9)
/DISP_SCL: J6.38, U9.3 (SCL1)
/DISP_SDA: J6.39, U9.4 (SDA1)
/DISP_VSYNC: J6.35, U4.11 (PI9), U8.2 (1A)
/DRA0: U1.23 (A0), U2.23 (A0), U4.16 (PF0)
/DRA1: U1.24 (A1), U2.24 (A1), U4.17 (PF1)
/DRA2: U1.25 (A2), U2.25 (A2), U4.18 (PF2)
/DRA3: U1.26 (A3), U2.26 (A3), U4.22 (PF3)
/DRA4: U1.29 (A4), U2.29 (A4), U4.23 (PF4)
/DRA5: U1.30 (A5), U2.30 (A5), U4.24 (PF5)
/DRA6: U1.31 (A6), U2.31 (A6), U4.71 (PF12)
/DRA7: U1.32 (A7), U2.32 (A7), U4.74 (PF13)
/DRA8: U1.33 (A8), U2.33 (A8), U4.75 (PF14)
/DRA9: U1.34 (A9), U2.34 (A9), U4.76 (PF15)
/DRA10: U1.22 (A10), U2.22 (A10), U4.77 (PG0)
/DRA11: U1.35 (A11), U2.35 (A11), U4.78 (PG1)
/DRA12: U1.36 (A12), U2.36 (A12), U4.129 (PG2)
/GREEN: J4.2, RN2.3 (R2), U5.32 (IOG)
/HSYNC: J4.13, U8.6 (2B)
/NBL0: U1.15 (DQML), U2.15 (DQML), U4.200 (PE0)
/NBL1: U1.39 (DQMH), U2.39 (DQMH), U4.201 (PE1)
/OP0: U4.104 (PB12), U11.1 (A1)
/OP1: U4.105 (PB13), U11.3 (A2)
/OP2: U4.106 (PB14), U11.4 (A3)
/OP3: U4.107 (PB15), U11.5 (A4)
/PARITY: U4.162 (PC11), U10.1 (A1)
/PDR_ON: RN1.4 (R3), SW2.7, U4.203 (PDR_ON)
/P_AD0: J3.a24 (AD0), U3.2 (1B0)
/P_AD1: J3.a25 (AD1), U3.3 (1B1)
/P_AD2: J3.a26 (AD2), U3.5 (1B2)
/P_AD3: J3.a27 (AD3), U3.6 (1B3)
/P_AD4: J3.a28 (AD4), U3.8 (1B4)
/P_AD5: J3.a29 (AD5), U3.9 (1B5)
/P_AD6: J3.a30 (AD6), U3.11 (1B6)
/P_AD7: J3.a31 (AD7), U3.12 (1B7)
/P_AD8: J3.a22 (AD8), U3.13 (2B0)
/P_AD9: J3.a21 (AD9), U3.14 (2B1)
/P_AD10: J3.a20 (AD10), U3.16 (2B2)
/P_AD11: J3.a19 (AD11), U3.17 (2B3)
/P_AD12: J3.a18 (AD12), U3.19 (2B4)
/P_AD13: J3.a17 (AD13), U3.20 (2B5)
/P_AD14: J3.a16 (AD14), U3.22 (2B6)
/P_AD15: J3.a15 (AD15), U3.23 (2B7)
/P_AD16: J3.c25 (AD16), U6.2 (1B0)
/P_AD17: J3.c24 (AD17), U6.3 (1B1)
/P_AD18: J3.c23 (AD18), U6.5 (1B2)
/P_AD19: J3.c22 (AD19), U6.6 (1B3)
/P_AD20: J3.c21 (AD20), U6.8 (1B4)
/P_AD21: J3.c20 (AD21), U6.9 (1B5)
/P_AD22: J3.c19 (AD22), U6.11 (1B6)
/P_AD23: J3.c18 (AD23), U6.12 (1B7)
/P_AD24: J3.c16 (AD24), U6.13 (2B0)
/P_AD25: J3.c15 (AD25), U6.14 (2B1)
/P_AD26: J3.c14 (AD26), U6.16 (2B2)
/P_AD27: J3.c13 (AD27), U6.17 (2B3)
/P_AD28: J3.c12 (AD28), U6.19 (2B4)
/P_AD29: J3.c11 (AD29), U6.20 (2B5)
/P_AD30: J3.c10 (AD30), U6.22 (2B6)
/P_AD31: J3.c9 (AD31), U6.23 (2B7)
/P_OP0: J3.a10 (OP0), U11.20 (B1)
/P_OP1: J3.a9 (OP1), U11.18 (B2)
/P_OP2: J3.a8 (OP2), U11.17 (B3)
/P_OP3: J3.a7 (OP3), U11.16 (B4)
/P_PARITY: J3.c31 (PAR), U10.20 (B1)
/P_SCL: J3.c5 (SCL), U12.6 (SCL2)
/P_SDA: J3.c4 (SDA), U12.5 (SDA2)
/RED: J4.1, RN2.2 (R1), U5.34 (IOR)
/SCL: U4.195 (PB6), U12.3 (SCL1)
/SDA: U4.196 (PB7), U12.4 (SDA1)
/SDCKE0: U1.37 (CKE), U4.38 (PC3_C)
/SDCKE1: U2.37 (CKE), U4.97 (PH7)
/SDCLK: U1.38 (CLK), U2.38 (CLK), U4.135 (PG8)
/SDQ0: U1.2 (DQ0), U2.2 (DQ0), U4.116 (PD14)
/SDQ1: U1.4 (DQ1), U2.4 (DQ1), U4.117 (PD15)
/SDQ2: U1.5 (DQ2), U2.5 (DQ2), U4.164 (PD0)
/SDQ3: U1.7 (DQ3), U2.7 (DQ3), U4.165 (PD1)
/SDQ4: U1.8 (DQ4), U2.8 (DQ4), U4.79 (PE7)
/SDQ5: U1.10 (DQ5), U2.10 (DQ5), U4.80 (PE8)
/SDQ6: U1.11 (DQ6), U2.11 (DQ6), U4.81 (PE9)
/SDQ7: U1.13 (DQ7), U2.13 (DQ7), U4.84 (PE10)
/SDQ8: U1.42 (DQ8), U2.42 (DQ8), U4.85 (PE11)
/SDQ9: U1.44 (DQ9), U2.44 (DQ9), U4.86 (PE12)
/SDQ10: U1.45 (DQ10), U2.45 (DQ10), U4.87 (PE13)
/SDQ11: U1.47 (DQ11), U2.47 (DQ11), U4.88 (PE14)
/SDQ12: U1.48 (DQ12), U2.48 (DQ12), U4.89 (PE15)
/SDQ13: U1.50 (DQ13), U2.50 (DQ13), U4.108 (PD8)
/SDQ14: U1.51 (DQ14), U2.51 (DQ14), U4.109 (PD9)
/SDQ15: U1.53 (DQ15), U2.53 (DQ15), U4.110 (PD10)
/TCK: J1.9 (TCK/SWDCLK), U4.159 (PA14)
/TDI: J1.5 (TDI), U4.160 (PA15)
/TDO: J1.13 (TDO/SWO), U4.192 (PB3)
/TMS: J1.7 (TMS/SWDIO), U4.147 (PA13)
/VSYNC: J4.14, U8.7 (1B)
/~CEN: U4.91 (PB11), U10.5 (A4)
/~CERR: U4.194 (PB5), U10.4 (A3)
/~CRDY: U4.198 (PB8), U10.6 (A5)
/~DACK: U4.140 (PC8), U10.8 (A7)
/~DS: U4.161 (PC10), U10.9 (A8)
/~INIT: U4.139 (PC7), U11.9 (A8)
/~IRQ: U4.199 (PB9), U11.8 (A7)
/~MRDY: U4.8 (PC13), U10.7 (A6)
/~PERR: U4.63 (PB2), U10.3 (A2)
/~PSAVE: RN1.3 (R2), SW2.6, U5.38 (~PSAVE)
/~P_CEN: J3.a13 (~CEN), U10.16 (B4)
/~P_CERR: J3.b3 (~CERR), U10.17 (B3)
/~P_CRDY: J3.a12 (~CDRDY), U10.15 (B5)
/~P_INIT: J3.a6 (~INIT), U11.12 (B8)
/~P_IRQ: J3.a4 (~IRQ), U11.13 (B7)
/~P_MRDY: J3.a11 (~MDRDY), U10.14 (B6)
/~P_PERR: J3.b4 (~PERR), U10.18 (B2)
/~P_RST: J3.c3 (~CRST), U11.14 (B6)
/~RST: C1.2, R1.2, SW1.2 (B), U4.34 (NRST), U11.7 (A6)
/~SDCAS: U1.17 (~CAS), U2.17 (~CAS), U4.191 (PG15)
/~SDEN0: U1.19 (~CS), U4.37 (PC2_C)
/~SDEN1: U2.19 (~CS), U4.96 (PH6)
/~SDRAS: U1.18 (~RAS), U2.18 (~RAS), U4.70 (PF11)
/~SDWE: U1.16 (~WE), U2.16 (~WE), U4.35 (PC0)
/~STOP: U4.163 (PC12), U11.6 (A5)
/~TRST: J1.3 (~TRST), U4.193 (PB4)
GND: C1.1, C4.2, C5.2, C6.2, C7.2, C8.2, C9.2, C10.2, C11.2, C12.2, C13.2, C14.2, C15.2, C16.2, C17.2, C18.2, C19.2, C22.2, C23.2, C24.2, C25.2, C26.2, C27.2, C28.2, C29.2, C30.2, C31.2, C32.2, C33.2, C34.2, C35.2, C36.2, C37.2, J1.4 (GND), J1.6 (GND), J1.8 (GND), J1.10 (GND), J1.12 (GND), J1.14 (GND), J1.16 (GND), J1.18 (GND), J1.20 (GND), J2.a1 (GND), J2.a10 (GND), J2.b1 (GND), J2.b5 (GND), J2.b6 (~PRES), J2.b10 (GND), J2.c1 (GND), J2.c10 (GND), J3.a1 (GND), J3.a2 (~PRES), J3.a5 (GND), J3.a14 (GND), J3.a23 (GND), J3.a32 (GND), J3.b1 (GND), J3.b2 (GND), J3.b5 (GND), J3.b14 (GND), J3.b23 (GND), J3.b32 (GND), J3.c1 (GND), J3.c8 (GND), J3.c17 (GND), J3.c26 (GND), J3.c28 (GND), J3.c32 (GND), J4.0, J4.5, J4.10, J6.1, J6.10, J6.11, J6.20, J6.21, J6.30, J6.31, J6.34, J6.37, J6.40, J6.MP (MountPin), RN1.1 (common), RN3.1 (common), SW1.1 (A), U1.6 (VSSQ), U1.12 (VSSQ), U1.28 (VSS), U1.41 (VSS), U1.46 (VSSQ), U1.52 (VSSQ), U1.54 (VSS), U2.6 (VSSQ), U2.12 (VSSQ), U2.28 (VSS), U2.41 (VSS), U2.46 (VSSQ), U2.52 (VSSQ), U2.54 (VSS), U4.14 (VSS), U4.25 (VSS), U4.40 (VSSA), U4.51 (VSS), U4.60 (VSS), U4.72 (VSS), U4.82 (VSS), U4.93 (VSS), U4.114 (VSS), U4.125 (VSS), U4.136 (VSS), U4.149 (VSS), U4.170 (VSS), U4.184 (VSS), U4.202 (VSS), U5.1 (G0), U5.2 (G1), U5.12 (~SYNC), U5.14 (B0), U5.15 (B1), U5.39 (R0), U5.40 (R1), U8.4 (GND), U9.1 (GND)
GNDA: C21.2, C38.2, C39.2, C40.2, C41.2, C42.2, C43.2, J4.6, J4.7, J4.8, R6.2, RN2.1 (common), U5.25 (GND), U5.26 (GND), U5.27 (~IOB), U5.31 (~IOG), U5.33 (~IOR), U7.2 (V-)
unnamed: C18.1, C19.1, U4.92 (VCAP), U4.148 (VCAP)
unnamed: J1.19 (DBGACK/NC), RN3.4 (R3)
unnamed: J1.17 (DBGRQ/NC), RN3.3 (R2)
unnamed: J1.11 (RTCK), RN3.2 (R1)
unnamed: C2.2, C3.2, U4.41 (VREF+)
unnamed: C20.1, U5.35 (COMP)
unnamed: R6.1, U5.37 (Rset)
unnamed: C21.1, R5.2, U5.36 (Vref), U7.1 (V+)
unnamed: R7.2, U9.8 (EN)
